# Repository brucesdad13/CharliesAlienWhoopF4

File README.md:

# UPDATE -- Charlie's AlienWhoop F4 is now OBSOLETE. A new version, deriving from [Lance's AlienFlight F3 Brushed Quad](https://github.com/brucesdad13/AlienFlightArchive/tree/master/Flight-Controllers/F3-V1/F3-Quad), based on the F7 processor has been developed. The AlienWhoop F7 board is backwards compatible, on the same PCB, with F4. The content below has been preserved for historical purposes. Please continue on to [AlienWhoop F7](https://github.com/brucesdad13/AlienWhoopF7)

# AlienWhoopF4 Features :alien:
AlienFlight F4 remixed for Tiny Whoop/Inductrix

* High-performance ST Microelectronics ARM Cortex-M4 core F4 168 MHz CPU
* Invensense MPU-9250 Nine-Axis (Gyro + Accelerometer + Compass) low power consumption MEMS MotionTracking™ Device
* Latest BetaFlight support (via ALIENFLIGHTF4 target) capable of 32kHz gyro sampling and 16kHz PID loop
* Fairchild Semiconductor FDMA410NZ MOSFET with 9.5A continuous and 24A burst brushed motor insanity (8.5mm coreless scream)

## DIY Flight Controller :alien:
Order your own PCBs from OSH Park by visiting the link below. I recommend ordering the 2oz copper 0.8mm thickness PCB. It takes about three weeks but that will allow plenty of time to order components from the bill of materials in the resources folder. I don't receive any commission or compesation when you order from OSH Park--simply created as a convenience to you (**Note: this version is now obsolete please see the AlienWhoop F7**).
* https://oshpark.com/

## Official Facebook page :alien:
Charlie's AlienWhoop F4 has a Facebook page:
* https://www.facebook.com/alienwhoop/

## See the AlienWhoop F4 in action on YouTube :alien:

May this work be of benefit and bring much joy and happiness!

## Acknowledgements :alien:

Deep bows of appreciation and thanks to Lance for his original work and tremendous
generosity in releasing his labor of love for the benefit of all flight controller
enthusiasts. Check out AlienWhoop's heritage at Lance's site:
* http://alienflight.com/ ~ offline as of June 2017
* https://github.com/brucesdad13/AlienFlightArchive ~ Archive of Lance's AlienFlight CC BY-SA suite of flight controllers

Equally deep bows to Jesse Perkins, creator of Tiny Whoop, and the source of inspiration and love for tiny brushed quads.
* http://www.tinywhoop.com/ ~
* https://www.facebook.com/groups/tinywhoop/ ~

Appreciation and respect also goes out to the contributors to the BetaFlight ALIENFLIGHTF4 target including Michael Jakob (MJ666), Martin Budden (martinbudden), and J Blackman (blckmn). Special thanks to Michael Jakob (MJ666) for clearing up confusion on the MPU-9250 magnetometer / compass driver and for updating to MPU-6500 code to work with whichever MPU you decide upon 6500 or 9250 (with compass).

Others deserving thanks for answering questions include in no specific order (and many others):
* OSH Park
* Adam Madron
* Joel Goetze
* Gary Baynes
* Peter (Pedro) Newman

~ Please note: AlienWhoop is not affiliated with nor endorsed by Lance (alienflight.com) or any other Alien projects. The use of Alien in the name and the alien head vector graphic used on the board silkscreen are nods to the lineage of this remix and to the work of Lance and others who created the conditions for this project to arise. Likewise, AlienWhoop is not affiliated with nor endorsed by Tiny Whoop. The Whoop in the name comes from Jesse Perkin's fantastic Tiny Whoop ("a small first-person-view aircraft that truly allows you to feel the gift of flight and the feeling of being tiny" [tinywhoop.com]) and is simply a nod to his efforts and the TW community worldwide.

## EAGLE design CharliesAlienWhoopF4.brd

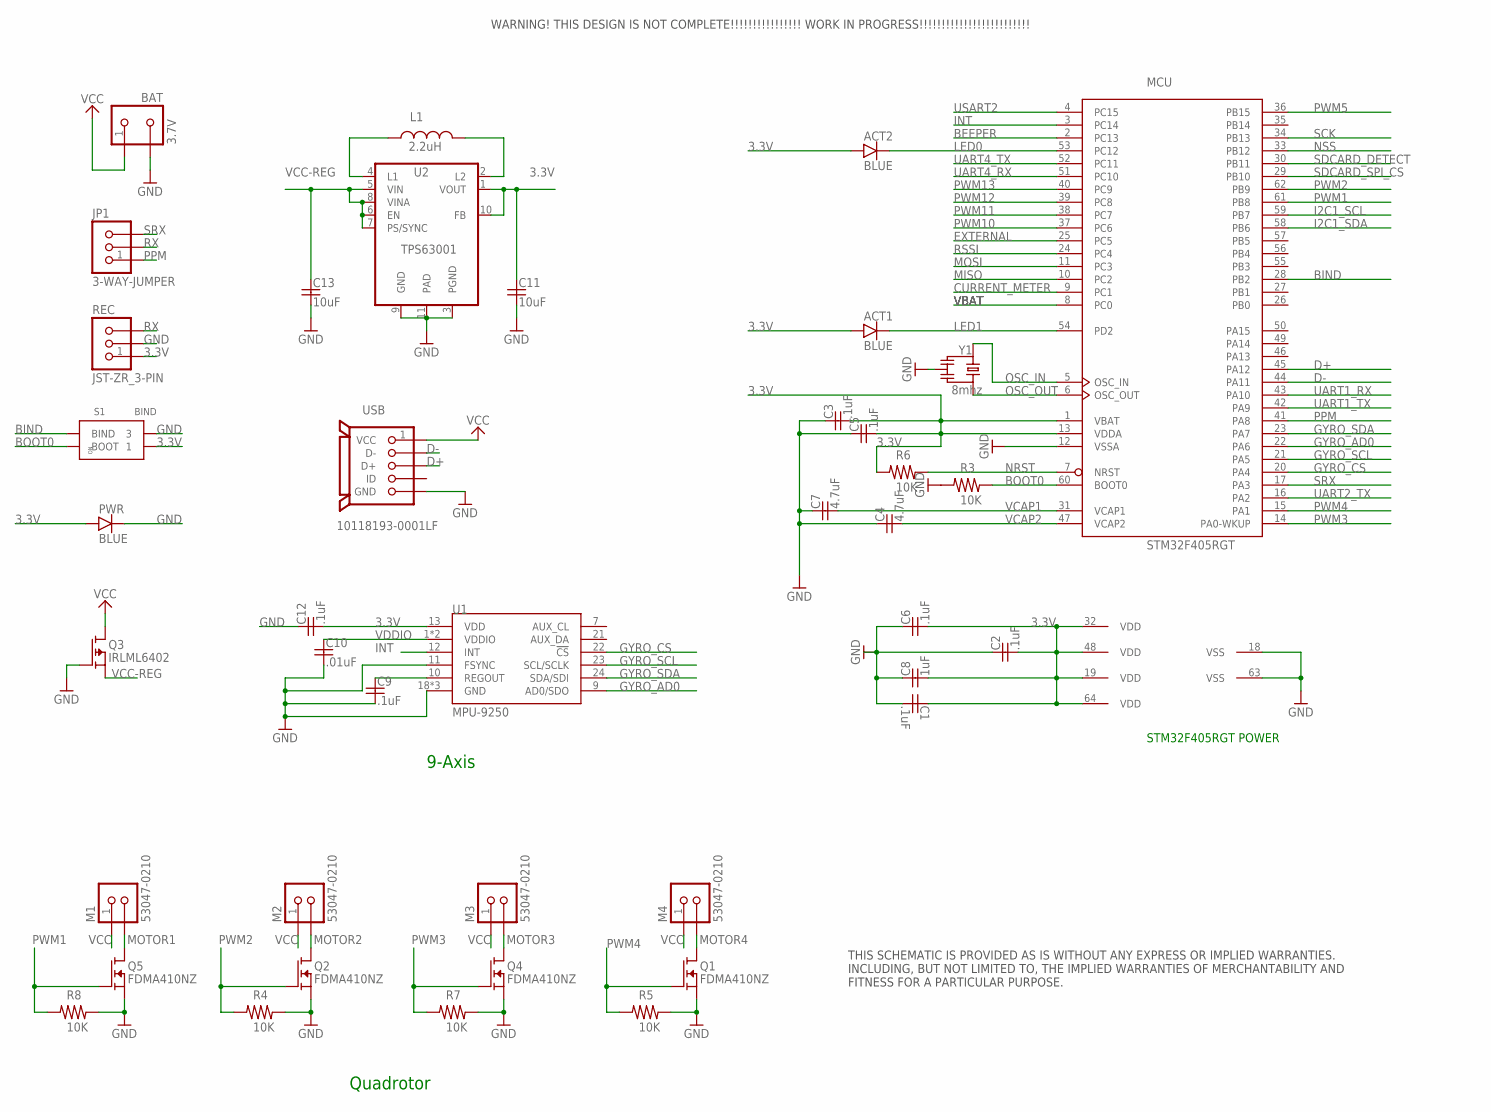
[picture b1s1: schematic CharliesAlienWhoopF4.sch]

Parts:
ACT1, ACT2: BLUE; SMD-CHIP-LED-0805
BAT: 3.7V; S2B-PH-K-S
C1, C2, C3, C5, C6, C9, C12: .1uF; MUR-CAP-0603
C4, C7: 4.7uF; MUR-CAP-0603
C8: 1uF; MUR-CAP-0603
C10: .01uF; MUR-CAP-0603
C11, C13: 10uF; YUDEN-CAP-0805
JP1: 3-WAY-JUMPER
L1: 2.2uH; NR301X
M1, M2, M3, M4: 53047-0210; PICO-53047-02
MCU: STM32F405RGT; LQFP64
PWR: BLUE; SMD-CHIP-LED-0805
Q1, Q2, Q4, Q5: FDMA410NZ; MICROFET-2X2
Q3: IRLML6402; SOT-23
R3, R4, R5, R6, R7, R8: 10K; VISH-RES-0603
REC: JST-ZR_3-PIN; S3B-ZR
S1: BIND; A6H-2101
U1: MPU-9250; QFN24_PAD
U2: TPS63001; VSON-N10
USB: 10118193-0001LF
Y1: 8mhz; RESONATOR_8

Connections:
3.3V: ACT1.A, ACT2.A, C1.1, C2.2, C3.2, C5.2, C6.2, C8.2, C11.1, C12.2, MCU.1 (VBAT), MCU.13 (VDDA), MCU.19 (VDD), MCU.32 (VDD), MCU.48 (VDD), MCU.64 (VDD), PWR.A, R6.2, REC.1, S1.BOOT_1 (1), U1.13 (VDD), U2.1 (VOUT), U2.10 (FB)
BEEPER: MCU.2 (PC13)
BIND: MCU.28 (PB2), S1.BIND_2 (BIND)
BOOT0: MCU.60 (BOOT0), R3.1, S1.BOOT_2 (BOOT)
CURRENT_METER: MCU.9 (PC1)
D+: MCU.45 (PA12), USB.3 (D+)
D-: MCU.44 (PA11), USB.2 (D-)
EXTERNAL: MCU.25 (PC5)
GND: BAT.2, C1.2, C2.1, C3.1, C4.1, C5.1, C6.1, C7.1, C8.1, C9.2, C10.2, C11.2, C12.1, C13.2, MCU.12 (VSSA), MCU.18 (VSS), MCU.63 (VSS), PWR.C, Q1.S, Q1.S1 (S), Q2.S, Q2.S1 (S), Q3.1 (G), Q4.S, Q4.S1 (S), Q5.S, Q5.S1 (S), R3.2, R4.1, R5.1, R7.1, R8.1, REC.2, S1.BIND_1 (3), U1.11 (FSYNC), U1.18 (GND), U1.20 (GND), U1.CENTER (GND), U2.3 (PGND), U2.9 (GND), U2.11 (PAD), USB.5 (GND), USB.GND, USB.GND2 (GND), USB.HOLE1 (GND), USB.HOLE2 (GND), Y1.2
GYRO_AD0: MCU.22 (PA6), U1.9 (AD0/SDO)
GYRO_CS: MCU.20 (PA4), U1.22 (!CS)
GYRO_SCL: MCU.21 (PA5), U1.23 (SCL/SCLK)
GYRO_SDA: MCU.23 (PA7), U1.24 (SDA/SDI)
I2C1_SCL: MCU.59 (PB7)
I2C1_SDA: MCU.58 (PB6)
INT: MCU.3 (PC14), U1.12 (INT)
L1: L1.1, U2.4 (L1)
L2: L1.2, U2.2 (L2)
LED0: ACT2.C, MCU.53 (PC12)
LED1: ACT1.C, MCU.54 (PD2)
MISO: MCU.10 (PC2)
MOSI: MCU.11 (PC3)
MOTOR1: M1.2, Q5.D, Q5.D1 (D), Q5.D2 (D), Q5.D3 (D), Q5.D4 (D)
MOTOR2: M2.2, Q2.D, Q2.D1 (D), Q2.D2 (D), Q2.D3 (D), Q2.D4 (D)
MOTOR3: M3.2, Q4.D, Q4.D1 (D), Q4.D2 (D), Q4.D3 (D), Q4.D4 (D)
MOTOR4: M4.2, Q1.D, Q1.D1 (D), Q1.D2 (D), Q1.D3 (D), Q1.D4 (D)
NRST: MCU.7 (NRST), R6.1
NSS: MCU.33 (PB12)
OSC_IN: MCU.5 (OSC_IN), Y1.1
OSC_OUT: MCU.6 (OSC_OUT), Y1.3
PPM: JP1.1, MCU.41 (PA8)
PWM1: MCU.61 (PB8), Q5.G, R8.2
PWM2: MCU.62 (PB9), Q2.G, R4.2
PWM3: MCU.14 (PA0-WKUP), Q4.G, R7.2
PWM4: MCU.15 (PA1), Q1.G, R5.2
PWM5: MCU.36 (PB15)
PWM10: MCU.37 (PC6)
PWM11: MCU.38 (PC7)
PWM12: MCU.39 (PC8)
PWM13: MCU.40 (PC9)
REGOUT: C9.1, U1.10 (REGOUT)
RSSI: MCU.24 (PC4)
RX: JP1.2, REC.3
SCK: MCU.34 (PB13)
SDCARD_DETECT: MCU.30 (PB11)
SDCARD_SPI_CS: MCU.29 (PB10)
SRX: JP1.3, MCU.17 (PA3)
UART1_RX: MCU.43 (PA10)
UART1_TX: MCU.42 (PA9)
UART2_TX: MCU.16 (PA2)
UART4_RX: MCU.51 (PC10)
UART4_TX: MCU.52 (PC11)
USART2: MCU.4 (PC15)
VBAT: MCU.8 (PC0)
VCAP1: C7.2, MCU.31 (VCAP1)
VCAP2: C4.2, MCU.47 (VCAP2)
VCC: BAT.1, M1.1, M2.1, M3.1, M4.1, Q3.3 (D), USB.1 (VCC)
VCC-REG: C13.1, Q3.2 (S), U2.5 (VIN), U2.6 (EN), U2.7 (PS/SYNC), U2.8 (VINA)
VDDIO: C10.1, U1.1 (VDDIO), U1.8 (VDDIO)

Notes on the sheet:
THIS SCHEMATIC IS PROVIDED AS IS WITHOUT ANY EXPRESS OR IMPLIED WARRANTIES. INCLUDING, BUT NOT LIMITED TO, THE IMPLIED WARRANTIES OF MERCHANTABILITY AND FITNESS FOR A PARTICULAR PURPOSE.
WARNING! THIS DESIGN IS NOT COMPLETE!!!!!!!!!!!!!!!! WORK IN PROGRESS!!!!!!!!!!!!!!!!!!!!!!!!!
STM32F405RGT POWER
9-Axis
Quadrotor

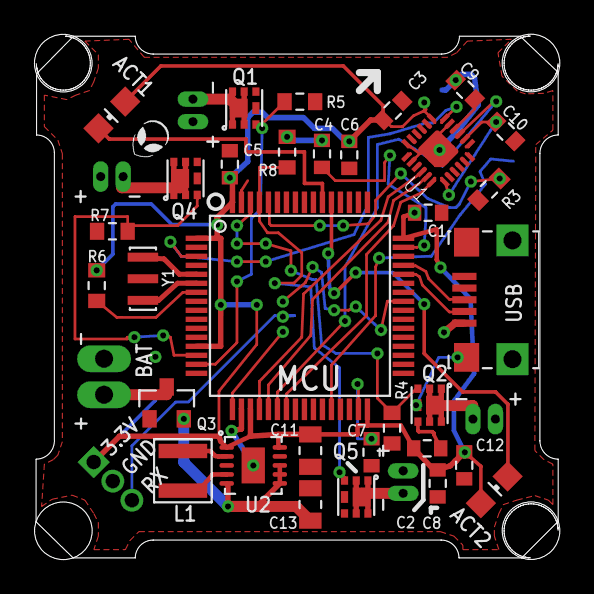
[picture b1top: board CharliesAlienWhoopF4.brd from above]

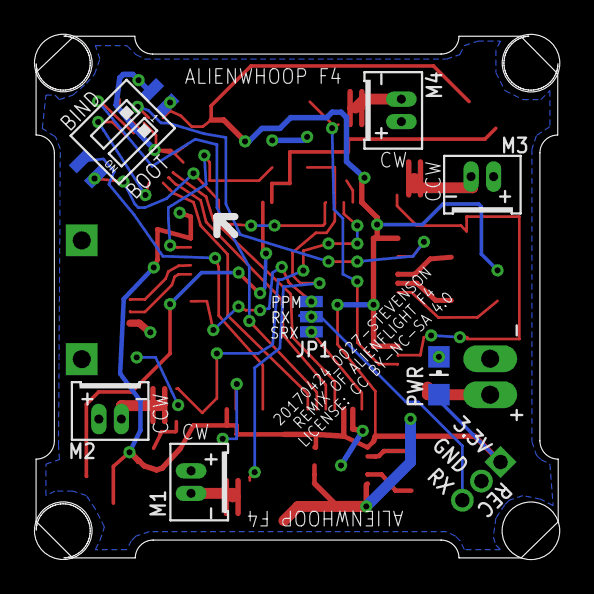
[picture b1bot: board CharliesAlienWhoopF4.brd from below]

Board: 2 copper layers, 29.0 x 29.0 mm, 41 parts (8 on the bottom side), 35 nets.

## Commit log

2017-03-14 Added project license
    Creative Commons Attribution-NonCommercial-ShareAlike 4.0 International inherited from AlienFlight F4 Brushed Quad project, of which this is a remix, http://alienflight.com/f4-brushed/
2017-03-14 Added ASCII art
2017-03-14 Updated markdown
2017-03-14 Gave up on ascii art for now... not quite groking the markdown
2017-03-14 Initial import of Eagle project. Cleaning up unused libraries etc.
2017-03-14 Added a few resources such as the mono bitmap for importing the alien head into silkscreen and a bill of materials/parts list spreadsheetwq
2017-03-14 Updated README with appreciation for Lance's pioneering AlienFlight designs and for his generosity in releasing the designs for all to learn from and enjoy.
2017-03-15 Added video of flight
2017-03-16 Fixed up libraries. Updated to latest version of Eagle
2017-03-16 I was having issues with solder bridges underneath the buckboost. Turns out my traces were too wide and when translated into gerber were leaving not much room for error. Hoping this makes reflow succ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
2017-03-16 Update README.md
    Added a link to the new Facebook page
2017-03-16 Reduced oscillator traces from 12mil to 11mil. Beginning to rearrange traces for aesthetics... ways to go...
2017-03-16 Initial Makefile with a convenient way to cleanup Eagle backups e.g. make clean
2017-03-16 Set theme jekyll-theme-hacker
2017-03-21 Removed duplicate board outline. Hopefully I got all the line segments. The second run of prototype boards from OSH park it appeared the cut was processed wrong or maybe they just used a larger bit t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
2017-03-21 Initial dump of AlienWhoop BetaFlight CLI configuration
2017-03-21 Updated date on silkscreen.
2017-03-25 Changed motor orientation back to 1 for my new favorite Furibee frame :)
2017-03-27 Update README.md
    Added video of AlienWhoop's racing debut
2017-04-02 Update README.md
    Added link to order PCB
2017-04-02 Added my current betaflight settings for the whoop.
2017-04-04 Update README.md
    Highlighted a few of the unique features that differentiate the AlienWhoop from other commercial offerings.
2017-04-04 Update README.md
    Embedded image of the board.
2017-04-04 Update README.md
    Added Alien Emoji (essential)
2017-04-04 Update README.md
    Added cover image
2017-04-05 Added configuration for the kids with the alienated foamdrones baby turtle :D
2017-04-08 Updated to remove reference to MPU-6050 and also to note that OMRON 2-position dip switch is sold out and backordered until June on most sites.
2017-04-10 Substituted the sealed version of the OMRON dip switch since the unsealed are backordered until June. Maybe they're trying to reduce inventory?
2017-04-10 Update README.md
    Added paypal.me link
2017-04-11 Added drill holes to address issue #1
2017-04-21 Update README.md
    Added special not thanking Michael Jakob for help getting the magnetometer driver situation sorted out.
2017-04-24 Fixed issue #1 mounting holes not drilled/cut. Thanks to advice from OSH Park's Dan Sheadel I'm now using an actual drill command and have redrawn the outline from scratch and am now cutting across t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
    Moved R3 silkscreen label since it was being hidden by a via.
    Ran ERC and DRC etc all passed. -CKS
2017-04-24 Update README.md
    Updated OSH Park link to latest revision with mounting holes fix.
2017-04-24 Update README.md
    Updated videos
2017-04-24 Latest settings... subject to change. Might want to reenable notch filters... -CKS
2017-05-20 Added another config with really low motor PWM rate. Loving the results... also dropped the custom mix that turned out to be extraneous thanks to FastEnuf
2017-06-15 Create README.md
    Removed hyperlink to closed Facebook group, "FC Builders and Hackers Cooperative", per moderator Peter Newman's request (@Pedro147) -CKS
2017-07-03 Update README.md
    Charlie's AlienWhoop F4 is now obsolete. See AlienWhoop F7
2017-07-17 Update README.md
    Some links are no longer working.. updated.
2017-08-11 Update README.md
    Added link to new project

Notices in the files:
CharliesAlienWhoopF4.brd:
Released under the Creative Commons Attribution-NonCommercial-ShareAlike 4.0 International License
https://creativecommons.org/licenses/by-nc-sa/4.0
LICENSE: CC BY-NC-SA 4.0
parts and their libraries:
alienflight: Released under the Creative Commons
http://creativecommons.org/licenses/by-nc-sa/4.0
alienflight: License: CC BY SA
